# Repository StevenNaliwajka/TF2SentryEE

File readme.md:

# NOT COMPLETE. In PROGRESS.

### To the ATF, It is structurally impossible for this design to be used with a real weapon and is not our goal. I am a law-abiding citizen.
### To Lockheed Martin, call me...
## Documentation is NOT complete. In progress
# TF2Sentry
This is the final piece of a project with [Maiikiru](https://github.com/Maiikiru) and Bradon
to create a fully functioning level one sentry from TF2 using an AIRSOFT gun.

Inbetween classes and work each of us have put countless hours into creating a cool project.

The work can be broken up into 3 repos.
- [Maiikiru's CV Repo](https://github.com/Maiikiru/TF2SentrySource) for the brain and the logic (PRIVATE for now)
- [Bradon's CAD Repo](https://github.com/ConvexBurrito5/TF2SentryCAD) for the physical CAD/STL files (PRIVATE for now)
- [Current Repo](https://github.com/ConvexBurrito5/TF2SentryEE) for circuitry and build instructions.

This repo is my work (Steven Naliwajka/ConvexBurrito5), [GitHub](https://github.com/ConvexBurrito5), [LinkedIn](https://www.linkedin.com/in/steven-naliwajka-69564929a/).

### Two options for targeting: 
1) Maiikiru has gone through and created a Computer vision (CV) repo that automatically detects and targets people: [Maiikiru's CV Repo](https://github.com/Maiikiru/TF2SentrySource)
2) I have also gone and created a remote control, [a slightly modified wrangler](https://www.youtube.com/watch?v=LYPzGNSfVRk)

To jump straight into building, see the Documentation folder.

## Review of my learned Skills
- At a high level, what we are trying to accomplish is simple however, as always, implementation is not as easy. I have learned lots:
  - Communication!
    - I2C Communication, learned how to implement and write code to utilize it in python.
    - Radio, utilizing 2.4Ghz wireless transceiver modules to talk from the turret to the wrangler
  - Power!
    - The turret and wrangler run off batteries.
    - 7.6v, 12v, 9.2v was all required. Got to use Buck DC voltage regulators.
    - Load calculation to make sure at least 5 hours of battery life.
  - Circuitry!
    - Circuitry to be able to plug in the turret without removing the battery. Same for Wrangler.
    - Performed proper wire size calculations; by working out max amps through each.
  - Coding!
    - Python - My first real project in python. I'm typically a java slob, so it was a little bit of a culture shock. But I'm glad I got to learn.
    - Arduino(C++) - Got to continue to hone my skills.
    - Git - I was dragged into the 21st century by Maiikiru. I'm proficient at Git now.
  - 3D Design!
    - Solidworks - I am competent at solidworks now.
  - Improved my 3D printing troubleshooting skills... and gotten a sizeable print farm out of it (2 decked out Ender 3s)
  - Working with Motors/Servos with control from both I2C and PWM.

With that out of the way, lets look into what we have completed.
## Features of the project
- Detection and tracking of a person, See [Maiikiru's CV Repo](https://github.com/Maiikiru/TF2SentrySource)
- We have provided [Maiikiru's CV Repo](https://github.com/Maiikiru/TF2SentrySource) with standard API interfaces so it easy to implement multiple hardware solutions. So far:
  - Raspberry Pi 5 (Please do not use a pi4, we tried to make it work, the performance is not good) , See 'instructionFT232H.md'
  - Standard laptop using [Adafruit's FT232H Breakout](https://www.adafruit.com/product/2264), See 'instructionRaspberryPi4.md'
- There are 4 interfaces implemented in each solution
  - FiringController
    - Handles the firing by pulling logic high on a switch to bridge the motor on the airsoft gun.
  - MotorController
    - Handles all motion. Basic set of methods to move your servos.
    - Idle motion, pans slowly looking for people.
  - PeripheralController
    - Handles the leds
  - SoundController
    - Handles all the sound, runs off of the devices default speaker.
- If a switch on the wrangler is turned on, automatic movement from [Maiikiru's CV Repo](https://github.com/Maiikiru/TF2SentrySource) will be disabled and overruled.
  - Input will be solely from the joystick and the firing button on the Wrangler.

## How can you build one?
Good news! Through many sleepless nights of documentation I have
compiled instructions to build your own TF2 Turret. You can begin by 
heading to the Documentation folder

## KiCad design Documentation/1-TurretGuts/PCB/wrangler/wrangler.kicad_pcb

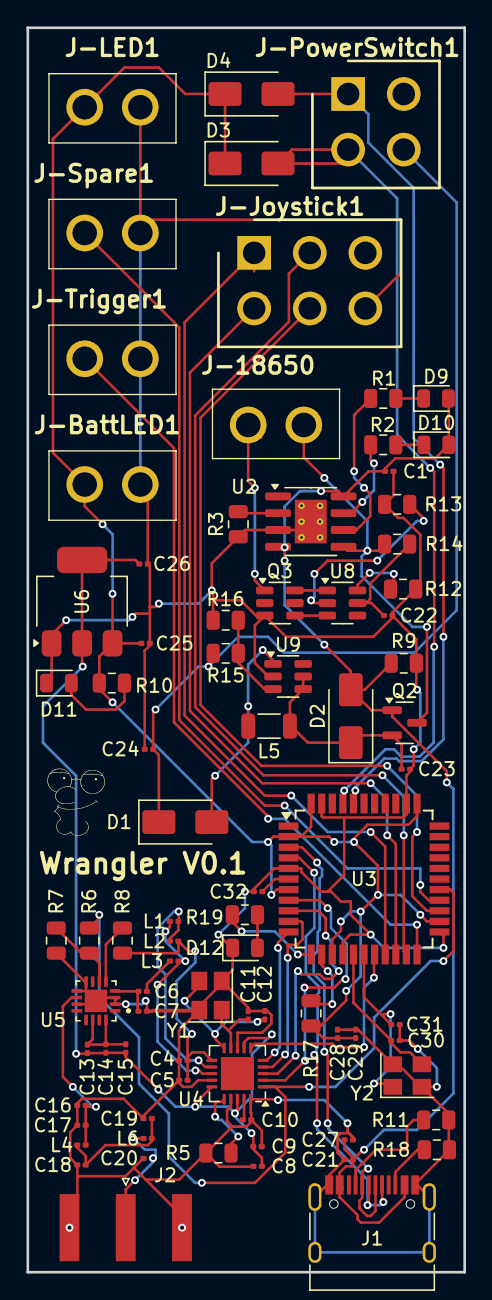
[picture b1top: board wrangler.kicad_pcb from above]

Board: 2 copper layers, 33.0 x 94.0 mm, 82 parts (0 on the bottom side), 60 nets.

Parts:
C1, C21, C22, C29, C32: .1uF; C_0201_0603Metric
C4: 2.2nF; C_0201_0603Metric
C5: 4.7pf; C_0201_0603Metric
C6: 1.5pF; C_0201_0603Metric
C7: 1.0pF; C_0201_0603Metric
C8, C14: 10nF; C_0201_0603Metric
C9: 1nF; C_0201_0603Metric
C10: 33nF; C_0201_0603Metric
C11, C12, C30, C31: 22pF; C_0201_0603Metric
C13: 220pF; C_0201_0603Metric
C15: 1uF; C_0201_0603Metric
C16: .3pF; C_0201_0603Metric
C17, C18, C19, C20: 1pF; C_0201_0603Metric
C23, C24: 22uF; C_0201_0603Metric
C25, C26, C27, C28: 10uF; C_0201_0603Metric
D1, D2, D3, D4: SS14; D_SMA
D9, D10, D11, D12: LED; LED_0805_2012Metric
J1: USB_C_Receptacle; USB_C_Receptacle_HRO_TYPE-C-31-M-12
J2: SMA-RP; SMA_Amphenol_132289_EdgeMount
J-18650: 35317-0221; 353170221
J-BattLED1: 35317-0221; 353170221
J-Joystick1: 35317-0620; RHDR6W107P420_2X3_1380X960X1310P
J-LED1: 35317-0221; 353170221
J-PowerSwitch1: 35317-0420; SHDR4W107P420_2X2_960X960X1280P
J-Spare1: 35317-0221; 353170221
J-Trigger1: 35317-0221; 353170221
L1: 8.2nH; C_0201_0603Metric
L2, L4, L6: 2.7nH; C_0201_0603Metric
L3: 3.9nH; C_0201_0603Metric
L5: 4.7uH; L_1206_3216Metric
Q2: AO3401A; SOT-23
Q3: FS8205A; SOT-23-6
R1, R2, R12, R13: 1K; C_0805_2012Metric
R3, R9: 1.2K; C_0805_2012Metric
R5: 22k; C_0805_2012Metric
R6, R8: 1k; C_0805_2012Metric
R7: 2k; C_0805_2012Metric
R10: 220; C_0805_2012Metric
R11, R18: 5.1K; C_0805_2012Metric
R14: 100; C_0805_2012Metric
R15: 32.4K; C_0805_2012Metric
R16, R17: 10K; C_0805_2012Metric
R19: 330; C_0805_2012Metric
U2: TP4056-42-ESOP8; SOIC-8-1EP_3.9x4.9mm_P1.27mm_EP2.41x3.3mm_ThermalVias
U3: ATmega32U4-A; TQFP-44_10x10mm_P0.8mm
U4: nRF24L01P; QFN-20-1EP_4x4mm_P0.5mm_EP2.5x2.5mm
U5: RFX2401C; QFN50P300X300X60-17N
U6: AMS1117; SOT-223-3_TabPin2
U8: DW01A; SOT-23-6
U9: MT3608; SOT-23-6
Y1, Y2: 16MHz; Crystal_SMD_3225-4Pin_3.2x2.5mm

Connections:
+3.3V: C8.1, C9.2, C13.2, C14.2, C15.2, C26.1, U4.7 (VDD), U4.15 (VDD), U4.18 (VDD), U6.2 (VO)
+5.3V: C24.2, D1.1 (K), J-PowerSwitch1.4, R15.2
+5V: C25.1, C28.1, C29.1, D3.1 (K), D4.1 (K), J-BattLED1.2, J-LED1.2, R10.2, R17.2, U3.2 (UVCC), U3.7 (VBUS), U3.14 (VCC), U3.24 (AVCC), U3.34 (VCC), U3.44 (AVCC), U6.3 (VI)
+V_Batt: J-18650.2, Q2.3 (D), R14.2, U2.5 (BAT)
-V_Batt: J-18650.1, Q3.1 (S1)
CE: R6.1, U3.27 (PD7), U4.1 (CE)
CSN: U3.8 (PB0), U4.2 (CSN)
D+: J1.A6 (D+), J1.B6 (D+), U3.4 (D+)
D-: J1.A7 (D-), J1.B7 (D-), U3.3 (D-)
GND: C1.2, C4.2, C5.2, C7.1, C8.2, C9.1, C10.2, C11.2, C12.2, C16.2, C17.2, C18.2, C19.2, C20.2, C21.1, C22.1, C23.2, C24.1, C25.2, C26.2, C27.2, C28.2, C29.2, C30.2, C31.2, C32.2, D11.1 (K), D12.1 (K), J1.A1 (GND), J1.A12 (GND), J1.B1 (GND), J1.B12 (GND), J1.S1 (SHIELD), J2.2 (Ext), J-BattLED1.1, J-Joystick1.6, J-LED1.1, J-Spare1.1, J-Trigger1.1, Q3.3 (S2), R3.1, R5.1, R7.1, R9.2, R11.1, R12.1, R13.2, R16.1, R18.1, U2.3 (GND), U2.9 (EPAD), U3.5 (UGND), U3.15 (GND), U3.23 (GND), U3.35 (GND), U3.43 (GND), U4.8 (VSS), U4.14 (VSS), U4.17 (VSS), U4.20 (VSS), U5.2 (GND), U5.3 (GND), U5.8 (GND), U5.9 (GND), U5.11 (GND), U5.17 (GND), U6.1 (ADJ), U9.2 (GND), Y1.2, Y1.4, Y2.2, Y2.4
GPIO1: J-Joystick1.1, U3.19 (PD1)
GPIO2: J-Joystick1.2, U3.20 (PD2)
GPIO3: J-Joystick1.3, U3.21 (PD3)
GPIO4: J-Joystick1.4, U3.25 (PD4)
GPIO5: J-Trigger1.2, U3.22 (PD5)
GPIO6: J-Spare1.2, U3.26 (PD6)
HighSwitch: D4.2 (A), J-PowerSwitch1.1, U3.40 (PF1)
IRQ: U3.18 (PD0), U4.6 (IRQ)
LowSwitch: D3.2 (A), J-PowerSwitch1.2, U3.41 (PF0)
MISO: U3.11 (PB3), U4.5 (MISO)
MOSI: U3.10 (PB2), U4.4 (MOSI)
unnamed: C6.1, L3.1
unnamed: C13.1, C14.1, C15.1, U5.14 (VDD), U5.16 (VDD)
unnamed: C18.1, C19.1, L4.2, L6.1
unnamed: D1.2 (A), L5.2, U9.1 (SW)
unnamed: C23.1, D2.1 (K), L5.1, Q2.2 (S), U9.4 (EN), U9.5 (IN)
unnamed: D9.1 (K), R1.2
unnamed: D10.1 (K), R2.2
unnamed: D11.2 (A), R10.1
unnamed: D12.2 (A), R19.2
unnamed: J1.A5 (CC1), R11.2
unnamed: J1.B5 (CC2), R18.2
unnamed: C20.1, J2.1 (In), L6.2
unnamed: Q3.6 (G1), U8.1 (OD)
unnamed: Q3.4 (G2), U8.3 (OC)
unnamed: R3.2, U2.2 (PROG)
unnamed: R2.1, U2.7 (~CHRG)
unnamed: R1.1, U2.6 (~STDBY)
unnamed: R19.1, U3.12 (PB7)
unnamed: C32.1, U3.6 (UCAP)
unnamed: C31.1, U3.17 (XTAL1), Y2.1
unnamed: C30.1, U3.16 (XTAL2), Y2.3
unnamed: R17.1, U3.13 (~RESET)
unnamed: L1.1, L2.2, U4.12 (ANT1)
unnamed: L1.2, L3.2, U4.13 (ANT2)
unnamed: C10.1, U4.19 (DVDD)
unnamed: R5.2, U4.16 (IREF)
unnamed: C12.1, U4.10 (XC1), Y1.3
unnamed: C11.1, U4.9 (XC2), Y1.1
unnamed: C16.1, C17.1, L4.1, U5.10 (ANT)
unnamed: R6.2, R7.2, U5.6 (RXEN)
unnamed: R8.1, U5.5 (TXEN)
unnamed: C6.2, C7.2, U5.4 (TXRX)
unnamed: R13.1, U8.2 (CS)
unnamed: R12.2, U8.6 (GND)
unnamed: C22.2, R14.1, U8.5 (VCC)
unnamed: R15.1, R16.2, U9.3 (FB)
SCK: U3.9 (PB1), U4.3 (SCK)
VDD_PA: C4.1, C5.1, L2.1, R8.2, U4.11 (VDD_PA)
Vusb: C1.1, C21.2, C27.1, D2.2 (A), D9.2 (A), D10.2 (A), J1.A4 (VBUS), J1.A9 (VBUS), J1.B4 (VBUS), J1.B9 (VBUS), Q2.1 (G), R9.1, U2.4 (V_{CC}), U2.8 (CE)

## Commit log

2024-12-19 Update the camera firmware
2024-12-20 Fix the camera code to actually return the type numpy is expecting
2024-12-20 Added camera_num param
2024-12-20 reorder parameters
2025-01-06 Change to use different sensor
2025-05-21 Added some more camera implementations
2025-05-21 Fixed small spacing errors
2025-05-21 Add more sensible defaults for left and right stereo map paths
2025-05-21 Correct for extra interface
2025-05-21 Fix the arducam implementation and remove empty file
2025-05-21 Modify the makeshift stereo camera to allow for setting the baseline and focal length later. This is useful for when you compute the value instead of using theoretical
2025-05-21 Fix ordering of params
2025-05-21 added matcher as an additional lazy value
2025-05-21 added better default values for stereo bm
2025-05-21 Correct the stereo calibrate method to use a generic stereo camera
2025-05-22 Make some more methods private and reorder order of methods in stereo_calibrate
2025-05-22 Change the load to be more efficient
2025-05-22 Save the arducam config
2025-05-24 add option to ignore dotted files
2025-05-24 Resolve a few imports
2025-05-24 Fix calib
2025-05-24 Fixed instantiation of abstract class
2025-05-24 Fix stereomatcher import
2025-05-25 Fix some errors
2025-05-25 Make more attributes private
2025-06-11 Update cameras to adhere to interfaces better
2025-07-07 add refs for Wrangler Circuit
2025-07-07 Wrangler PCB
2025-07-09 Migrated all of the implementation code over.
    Still needs to be tested!!!
    - Moved all implementation code over to main repo
    - Wrote Builders to build some of the more complicated interfaces
    - Migrated this repo to an actual python package which can be installed.
2025-07-09 Create LICENSE
2025-07-10 Fix the broken paths
2025-07-17 sync with main
2025-07-21 wrangler pass 1
2025-08-03 Still unstable, need to test camera interfaces
2025-08-05 move work from laptop to pc
2025-08-22 Added todos
2025-08-30 Need to fix some bugs. Moving to pc
